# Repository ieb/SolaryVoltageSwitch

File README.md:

# Voltage Switch

Originally this code was written as a voltage switch for a lead acid batter, connected to a solar pannel, that would turn on when the voltage is high, and off when low. For years it powered a pond pump, but my wife got super annoyed by the large 12v battery in the flower bed.

This is 2023, and there are lithium batters.
Acer laptop battery packs are 11.1v at 7K Ah with a TI BQ4050 Lipo state of charge chip. The chip is on I2C so the code has 
been rewitten to use this chip basing the turn on and turn off points on the state of chage. On above 70% provided the solar volate is > 12V, and off when < 30% or if the solar volate drops below 11.5v (ie its dark)

The LED flashes once the pump is on and 2x when its off.

# Battery

I am using a 9x18650 Acer batter pack with a BMS controlled by a TI BQ4050 chip. (chip data sheet. https://www.ti.com/lit/ug/sluuaq3a/sluuaq3a.pdf)

The BMS is probably a cheap clone. With the packs feet on the ground looking at the pack the pins are

     |   | 1 | 2 | 3 | 4 | 5 | 6 | 7 | 8 |   |
     -----------------------------------------

1,2 BatV+
3   ID  - Currently not known
4   ID  - Currently purpose not known
5   SDA
6   SCL
7   0V
8   0V

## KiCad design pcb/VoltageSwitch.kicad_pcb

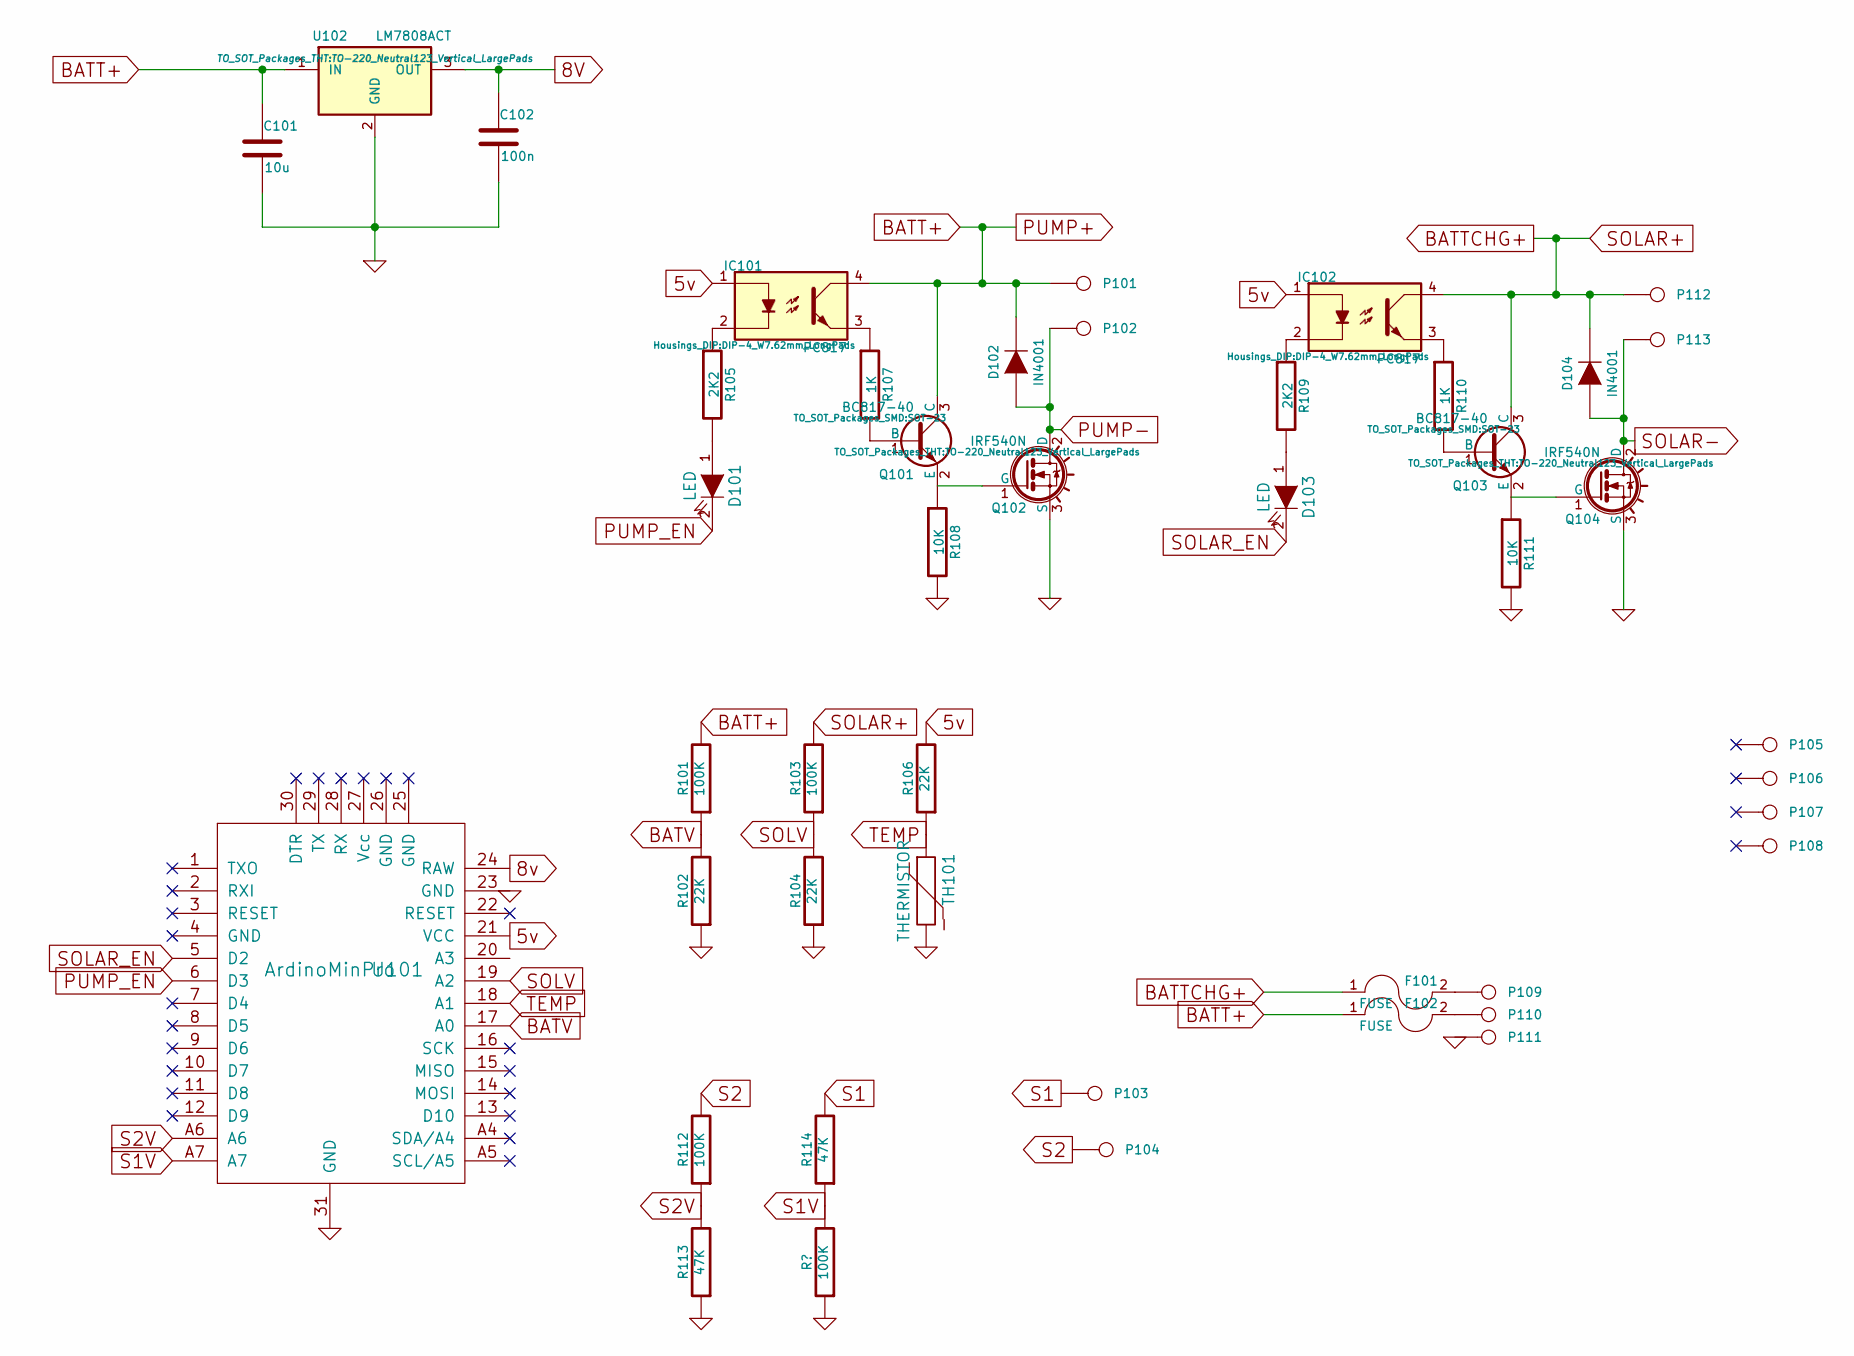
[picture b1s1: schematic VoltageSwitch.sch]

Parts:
C101: 10u; C_0805_HandSoldering
C102: 100n; C_0805_HandSoldering
D101, D103: LED; LED_0805
D102, D104: IN4001; D_0805
F101, F102: FUSE; BladeFuse-CarType
IC101, IC102: PC817; DIP-4_W7.62mm_LongPads
P101: Pump+; SolderWirePad_single_2mmDrill
P102: Pump-; SolderWirePad_single_2mmDrill
P103: S1; SolderWirePad_single_2mmDrill
P104: S2; SolderWirePad_single_2mmDrill
P105, P106, P107, P108: CONN_1; MountingHole_3.2mm_M3_ISO7380
P109: BatCharge+; SolderWirePad_single_2mmDrill
P110: BatTerm+; SolderWirePad_single_2mmDrill
P111: Bat-Term; SolderWirePad_single_2mmDrill
P112: Solar+; SolderWirePad_single_2mmDrill
P113: Solar-; SolderWirePad_single_2mmDrill
Q101, Q103: BC817-40; SOT-23
Q102, Q104: IRF540N; TO-220_Neutral123_Vertical_LargePads
R101, R103, R112: 100K; R_0805_HandSoldering
R102, R104, R106: 22K; R_0805_HandSoldering
R105, R109: 2K2; R_0805_HandSoldering
R107, R110: 1K; R_0805_HandSoldering
R108, R111: 10K; R_0805_HandSoldering
R113, R114: 47K; R_0805_HandSoldering
TH101: THERMISTOR; Resistor_Vertical_RM5mm
U101: ArdinoMinPro; ArduinoProMini
U102: LM7808ACT; TO-220_Neutral123_Vertical_LargePads

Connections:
5v: IC101.1, IC102.1, R106.2, U101.21 (VCC)
8V: C102.1, U101.24 (RAW), U102.3 (OUT)
BATT+: C101.1, D102.2 (K), F102.1, IC101.4, P101.1, Q101.3 (C), R101.2, U102.1 (IN)
BATTCHG+: D104.2 (K), F101.1, IC102.4, P112.1, Q103.3 (C), R103.2
BATV: R101.1, R102.2, U101.17 (A0)
GND: C101.2, C102.2, P111.1, Q102.3 (S), Q104.3 (S), R102.1, R104.1, R108.2, R111.2, R113.1, TH101.2, U101.23 (GND), U101.31 (GND), U102.2 (GND)
unnamed: D101.1 (A), R105.2
unnamed: D103.1 (A), R109.2
unnamed: F101.2, P109.1
unnamed: F102.2, P110.1
unnamed: IC101.2, R105.1
unnamed: IC101.3, R107.1
unnamed: IC102.2, R109.1
unnamed: IC102.3, R110.1
unnamed: Q101.1 (B), R107.2
unnamed: Q101.2 (E), Q102.1 (G), R108.1
unnamed: Q103.1 (B), R110.2
unnamed: Q103.2 (E), Q104.1 (G), R111.1
PUMP-: D102.1 (A), P102.1, Q102.2 (D)
PUMP_EN: D101.2 (K), U101.6 (D3)
S1: P103.1, R114.2
S1V: R114.1, U101.A7
S2: P104.1, R112.2
S2V: R112.1, R113.2, U101.A6
SOLAR-: D104.1 (A), P113.1, Q104.2 (D)
SOLAR_EN: D103.2 (K), U101.5 (D2)
SOLV: R103.1, R104.2, U101.19 (A2)
TEMP: R106.1, TH101.1, U101.18 (A1)

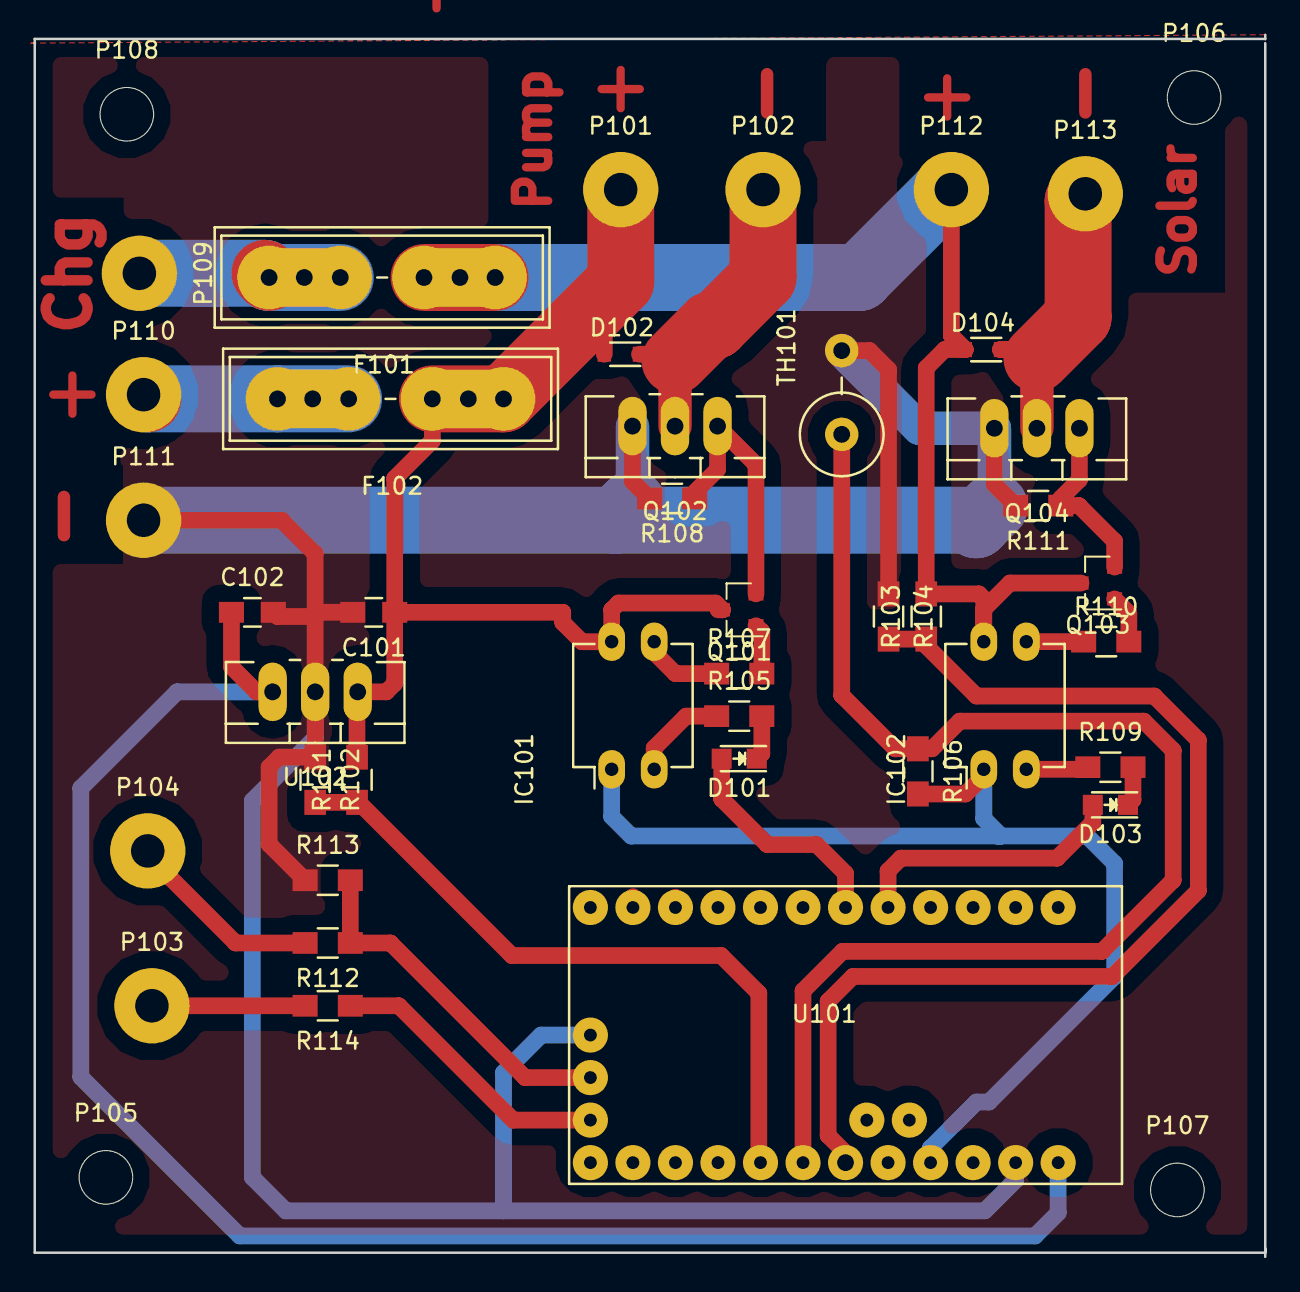
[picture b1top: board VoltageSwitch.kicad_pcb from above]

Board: 2 copper layers, 73.5 x 73.0 mm, 44 parts (0 on the bottom side), 28 nets.

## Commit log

2021-04-05 Initial commit of working code
2023-03-24 Now using a Lipo batter pack and smb chip
2023-04-07 Mk2 operational
2023-09-09 Fixed 49day overflows
